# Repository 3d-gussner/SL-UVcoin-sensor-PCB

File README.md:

# PRUSA SL UV coin sensor board

KiCad PCB layout

* [Interactive bom](http://htmlpreview.github.io/?https://github.com/prusa3d/SL-UVcoin-sensor-PCB/blob/master/rev.01/ibom.html)
* [STEP 3D model](rev.01/uv-sensor-analog-01.step)

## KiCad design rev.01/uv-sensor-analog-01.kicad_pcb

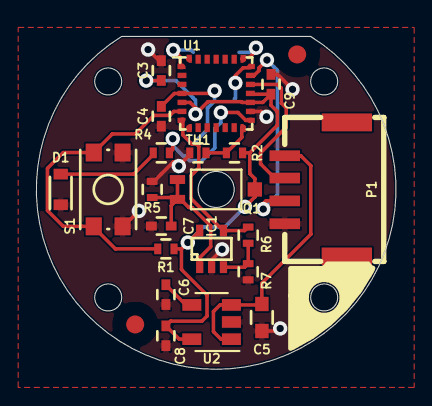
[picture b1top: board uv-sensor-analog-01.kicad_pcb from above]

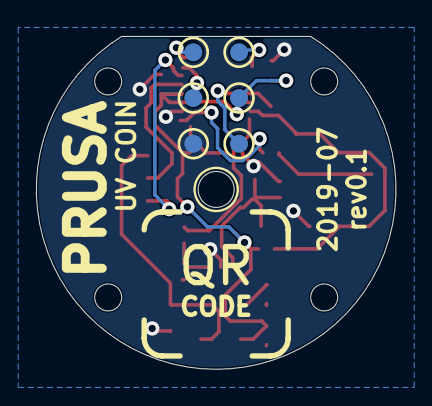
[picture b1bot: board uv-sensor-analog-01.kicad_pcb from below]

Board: 2 copper layers, 20.0 x 18.5 mm, 34 parts (9 on the bottom side), 17 nets.

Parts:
C3, C4, C9: 100n; C_0402
C5: 10u; C_0603
C6: 470p; C_0402
C7, C8: 1u; C_0402
D1: RF-OUB191TS-CE*; D_0603
IC1: LMV321M7; SC-70-5
M1: QRcode*; QR-code-8x8mm
MK1, MK2: Fiducial*; Fiducial_1mm_Dia_2.54mm_Outer_CopperBottom
MK3, MK4, MK5, MK6: MP*; MountingHole_2.2mm_M2
P1: MX 502382-0470; MX-502382-0470
Q1: SFH 3410R; Phototransistor_SFH3410R-2
R1: 10k*; R_0402
R2: 150k; R_0402
R4: 1k*; R_0402
R5, R6, R7: 10k; R_0402
S1: Y78B44110FP*; SW_SPST_KMR2
TH1: NTCG104LH104JTDS; R_0402
U1: STM32F042G6U6; UFQFPN-28
U2: TC1185-3.3; SOT-23-5
U$1, U$2, U$3, U$4, U$5, U$6: TESTPOINTTESTPADSMD; smd-point

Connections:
+3V3: C3.1, C8.2, C9.2, IC1.5, Q1.1, R1.2, R2.2, U1.5, U1.17, U1.18, U2.5, U$2.1
+5V: C5.2, P1.1, U2.1, U2.3
/ADC1: IC1.4, R6.2, U1.7
/BOOT: U1.1, U$1.1
/RST: C4.2, U1.4, U$4.1
/SWCLK: U1.22, U$6.1
/SWDIO: U1.21, U$5.1
GND: C3.2, C4.1, C5.1, C6.1, C7.1, C8.1, C9.1, D1.1, IC1.2, P1.4, R5.1, R7.1, S1.2, TH1.2, U1.16, U2.2, U$3.1
unnamed: C6.2, U2.4
unnamed: C7.2, IC1.1, Q1.2, R5.2
unnamed: D1.2, R4.1
unnamed: IC1.3, R6.1, R7.2
unnamed: P1.2, U1.19
unnamed: P1.3, U1.20
unnamed: R1.1, S1.1, U1.6
unnamed: R2.1, TH1.1, U1.14
unnamed: R4.2, U1.15
